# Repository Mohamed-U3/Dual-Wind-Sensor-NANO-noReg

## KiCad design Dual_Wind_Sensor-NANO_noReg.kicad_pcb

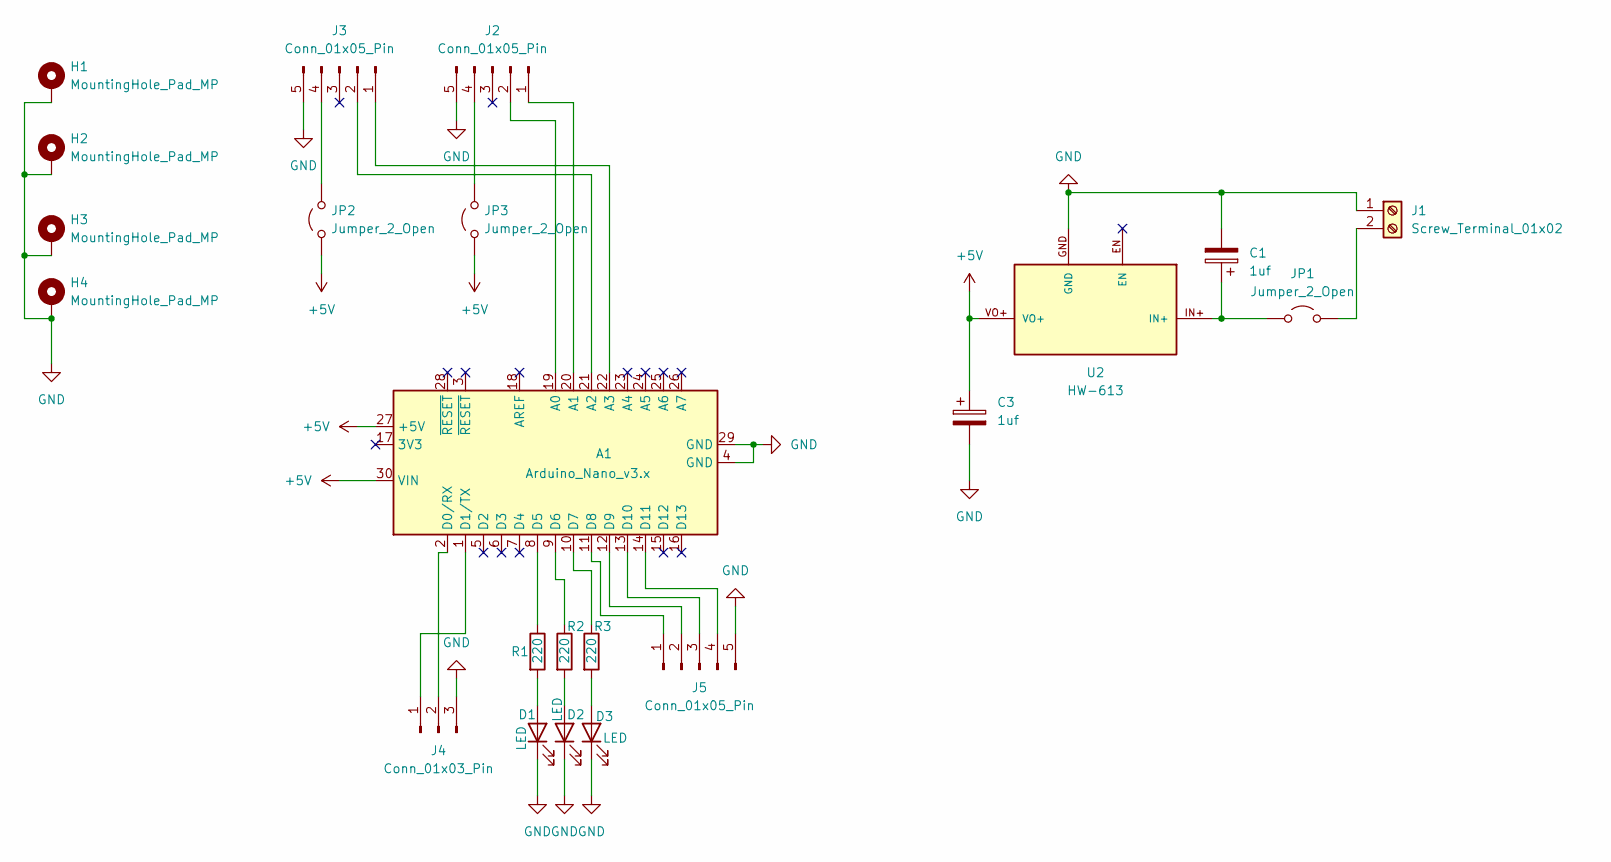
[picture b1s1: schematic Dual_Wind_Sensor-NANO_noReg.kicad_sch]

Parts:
A1: Arduino_Nano_v3.x; Arduino_Nano
C1, C3: 1uf; CP_Radial_D6.3mm_P2.50mm
D1, D2, D3: LED; LED_D5.0mm
H1, H2, H3, H4: MountingHole_Pad_MP; MountingHole_2.5mm_Pad_Via
J1: Screw_Terminal_01x02; Altech_AK100_1x02_P5.00mm
J2, J3, J5: Conn_01x05_Pin; JST_EH_B5B-EH-A_1x05_P2.50mm_Vertical
J4: Conn_01x03_Pin; JST_EH_B3B-EH-A_1x03_P2.50mm_Vertical
JP1, JP2, JP3: Jumper_2_Open; PinHeader_1x02_P2.54mm_Vertical
R1, R2, R3: 220; R_Axial_DIN0204_L3.6mm_D1.6mm_P5.08mm_Horizontal
U2: HW-613

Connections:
+5V: A1.27 (+5V), A1.30 (VIN), C3.1, JP2.1 (A), JP3.1 (A), U2.VO+
GND: A1.4 (GND), A1.29 (GND), C1.2, C3.2, D1.1 (K), D2.1 (K), D3.1 (K), H1.MP, H2.MP, H3.MP, H4.MP, J1.1, J2.5, J3.5, J4.3, J5.5, U2.GND
unnamed: A1.19 (A0), J2.2
unnamed: A1.20 (A1), J2.1
unnamed: A1.21 (A2), J3.2
unnamed: A1.22 (A3), J3.1
unnamed: A1.2 (D0/RX), J4.2
unnamed: A1.1 (D1/TX), J4.1
unnamed: A1.8 (D5), R1.1
unnamed: A1.9 (D6), R2.1
unnamed: A1.10 (D7), R3.1
unnamed: A1.11 (D8), J5.1
unnamed: A1.12 (D9), J5.2
unnamed: A1.13 (D10), J5.3
unnamed: A1.14 (D11), J5.4
unnamed: D1.2 (A), R1.2
unnamed: D2.2 (A), R2.2
unnamed: D3.2 (A), R3.2
unnamed: J1.2, JP1.2 (B)
unnamed: J2.4, JP3.2 (B)
unnamed: J3.4, JP2.2 (B)
unnamed: C1.1, JP1.1 (A), U2.IN+

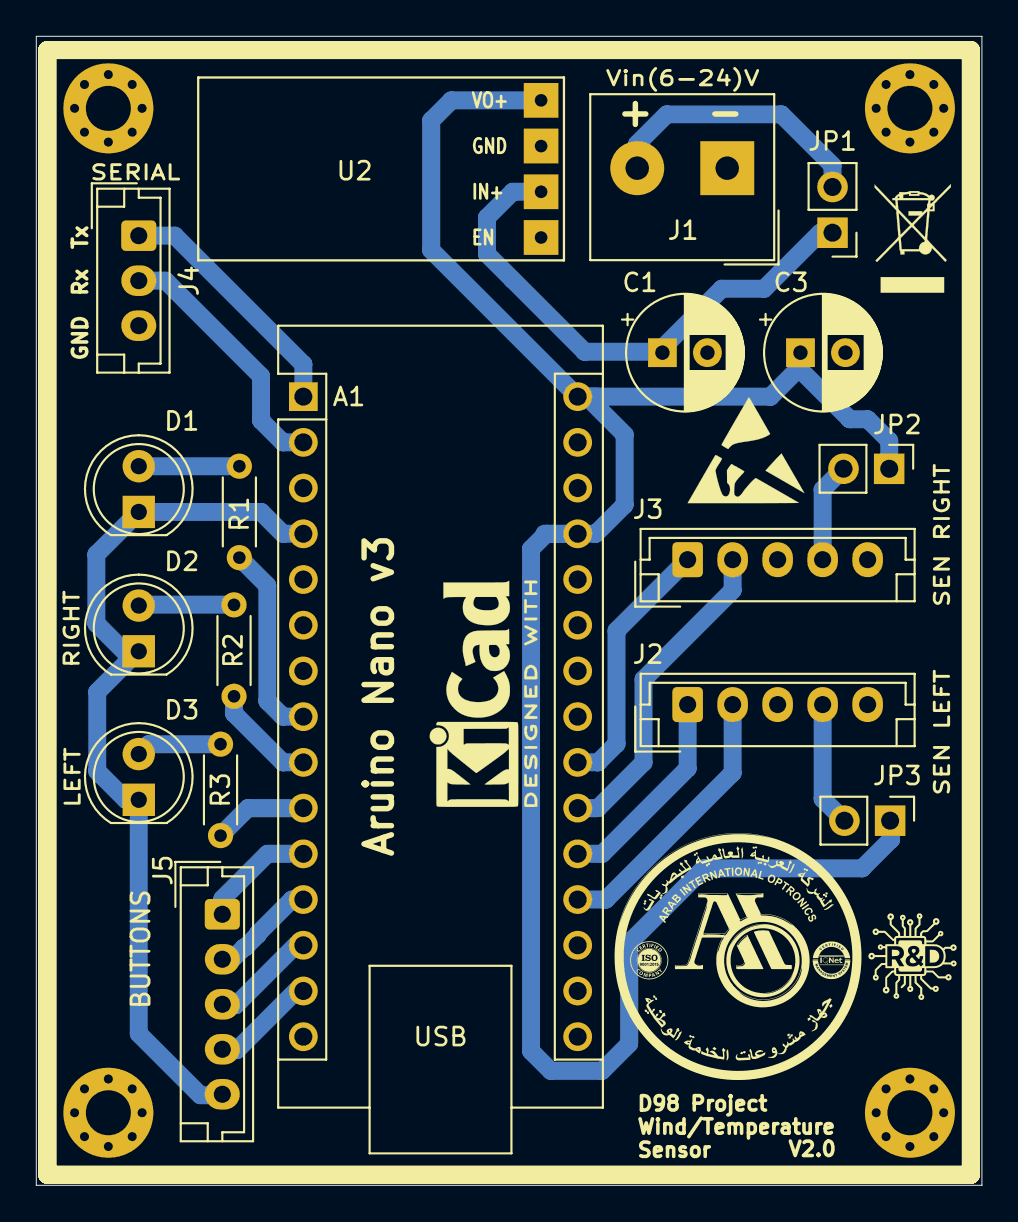
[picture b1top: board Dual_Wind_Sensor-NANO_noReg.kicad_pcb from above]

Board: 4 copper layers, 52.5 x 63.8 mm, 22 parts (0 on the bottom side), 22 nets.

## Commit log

2025-07-02 init commit for Kicad project of Dual Wind Sensor NANO noReg what I did is, modifiing the PCB design for this circuit in order to add a 5 pin JST connector for the 4 buttons. + making some modificati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
2025-07-08 very small change in the PCB.
